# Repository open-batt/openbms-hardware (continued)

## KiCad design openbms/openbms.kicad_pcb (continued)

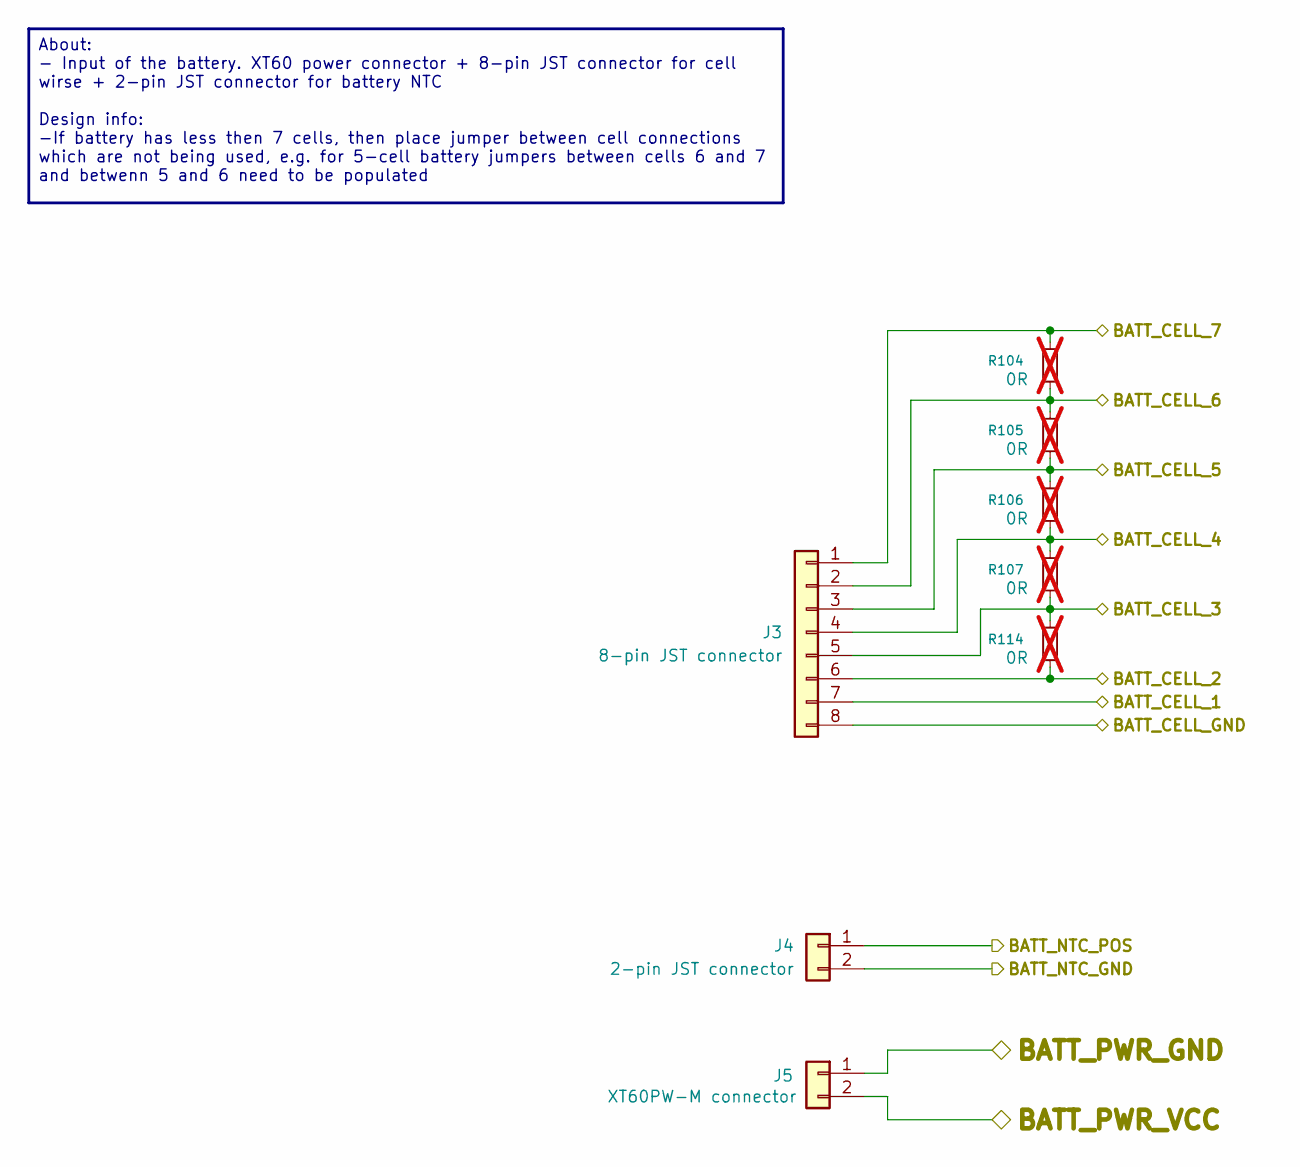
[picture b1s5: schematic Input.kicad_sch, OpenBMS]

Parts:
J3: 8-pin JST connector; JST_XH_S8B-XH-A_1x08_P2.50mm_Horizontal; Manufacturer_Part_Number S8B-XH-A
J4: 2-pin JST connector; JST_XH_S2B-XH-A_1x02_P2.50mm_Horizontal; Manufacturer_Part_Number S2B-XH-A
J5: XT60PW-M connector; AMASS_XT60PW-M_1x02_P7.20mm_Horizontal; Manufacturer_Part_Number XT60PW-M
R104, R105, R106, R107, R114: 0R; R_0402_1005Metric; Manufacturer_Part_Number CR0402AJ/-000GAS; not fitted

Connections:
+3V3: J4.1; also elsewhere on the board
/ADC/BATT_CS_POS: J5.1; also elsewhere on the board
/ADC/CELL_1: J3.7; also elsewhere on the board
/ADC/CELL_2: J3.6, R114.2; also elsewhere on the board
/ADC/CELL_3: J3.5, R107.2, R114.1; also elsewhere on the board
/ADC/CELL_4: J3.4, R106.2, R107.1; also elsewhere on the board
/ADC/CELL_5: J3.3, R105.2, R106.1; also elsewhere on the board
/ADC/CELL_6: J3.2, R104.2, R105.1; also elsewhere on the board
/ADC/CELL_7: J3.1, R104.1; also elsewhere on the board
/FETs/BATT_PWR_VCC: J5.2; also elsewhere on the board
/MCU/NTC: J4.2; also elsewhere on the board
GND_BATT_CELL: J3.8; also elsewhere on the board

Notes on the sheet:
About: - Input of the battery. XT60 power connector + 8-pin JST connector for cell wirse + 2-pin JST connector for battery NTC Design info: -If battery has less then 7 cells, then place jumper between cell connections which are not being used, e.g. for 5-cell battery jumpers between cells 6 and 7 a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

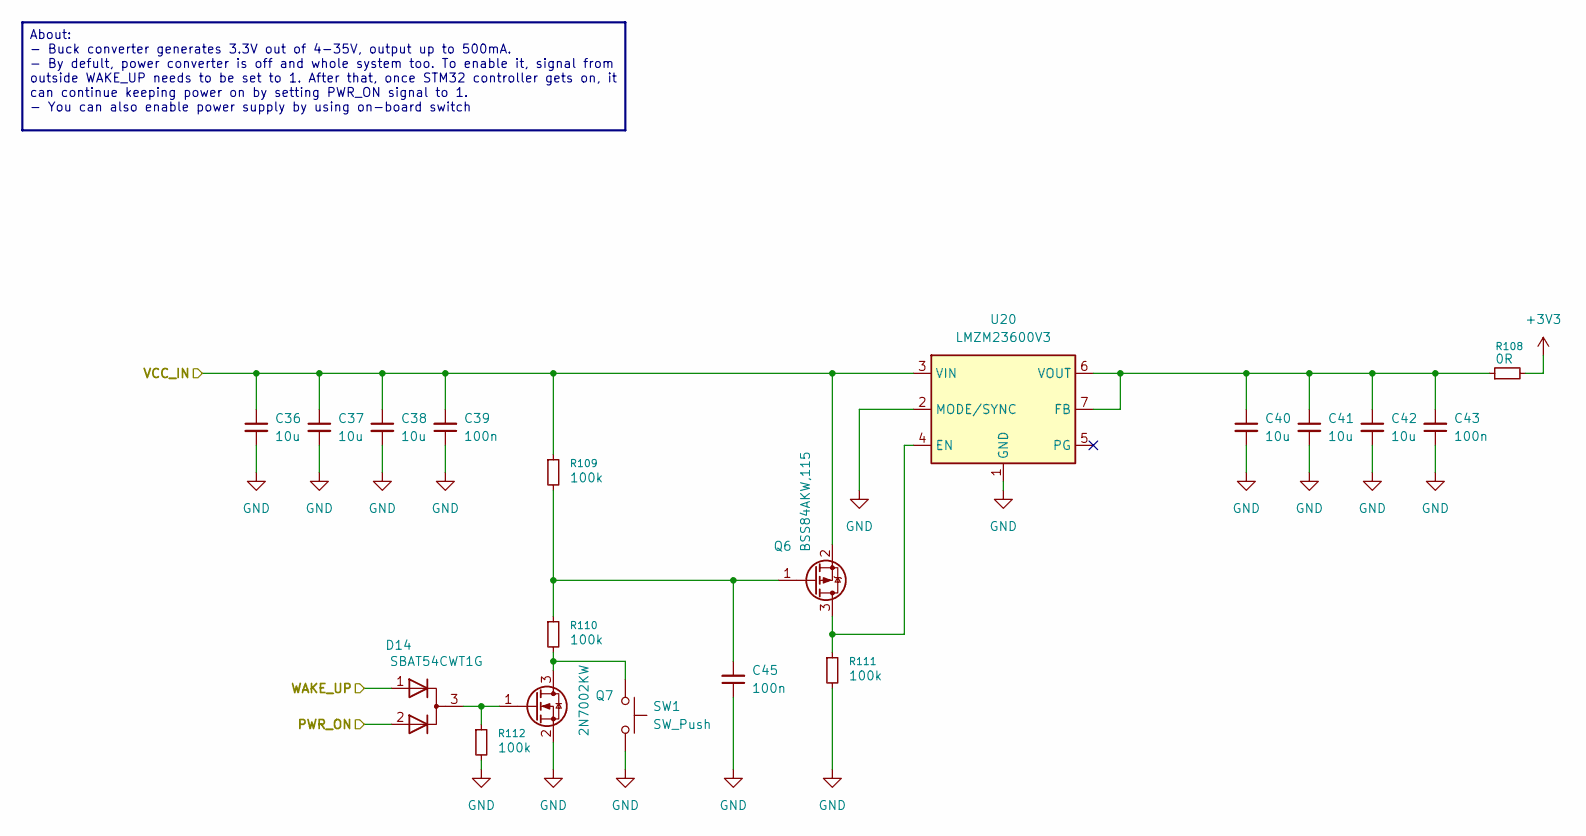
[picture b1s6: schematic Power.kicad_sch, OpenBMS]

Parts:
C36, C37, C38, C40, C41, C42: 10u; C_1206_3216Metric; Manufacturer_Part_Number CL31A106MBHNNNE
C39, C43, C45: 100n; C_0402_1005Metric; Manufacturer_Part_Number GRM155R71A104KA01D
D14: SBAT54CWT1G; SOT-323_SC-70; Manufacturer_Part_Number SBAT54CWT1G
Q6: BSS84AKW,115; SOT-323_SC-70; Manufacturer_Part_Number BSS84AKW,115
Q7: 2N7002KW; SOT-323_SC-70; Manufacturer_Part_Number 2N7002KW
R108: 0R; R_0402_1005Metric; Manufacturer_Part_Number CR0402AJ/-000GAS
R109, R110, R111, R112: 100k; R_0402_1005Metric; Manufacturer_Part_Number RC0402FR-07100KL
SW1: SW_Push; 435451019820; Manufacturer_Part_Number 435451019820
U20: LMZM23600V3; Texas_SIL0010A_MicroSiP-10-1EP_3.8x3mm_P0.6mm_EP0.7x2.9mm_T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; Manufacturer_Part_Number LMZM23600V3SILR

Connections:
+3V3: R108.2; also elsewhere on the board
/FETs/BATT_PWR_VCC_FUSED: C36.1, C37.1, C38.1, C39.2, Q6.2 (S), R109.1, U20.3 (VIN); also elsewhere on the board
/MCU/PWR_ON: D14.2 (A); also elsewhere on the board
/MCU/WAKE_UP: D14.1 (A); also elsewhere on the board
GND: C36.2, C37.2, C38.2, C39.1, C40.2, C41.2, C42.2, C43.1, C45.1, Q7.2 (S), R111.2, R112.2, SW1.2, U20.1 (GND), U20.2 (MODE/SYNC), U20.11 (GND); also elsewhere on the board
unnamed: D14.3 (K), Q7.1 (G), R112.1
unnamed: Q6.3 (D), R111.1, U20.4 (EN)
unnamed: C45.2, Q6.1 (G), R109.2, R110.1
unnamed: Q7.3 (D), R110.2, SW1.1
unnamed: C40.1, C41.1, C42.1, C43.2, R108.1, U20.6 (VOUT), U20.7 (FB)

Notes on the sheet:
About: - Buck converter generates 3.3V out of 4-35V, output up to 500mA. - By defult, power converter is off and whole system too. To enable it, signal from outside WAKE_UP needs to be set to 1. After that, once STM32 controller gets on, it can continue keeping power on by setting PWR_ON signal to 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

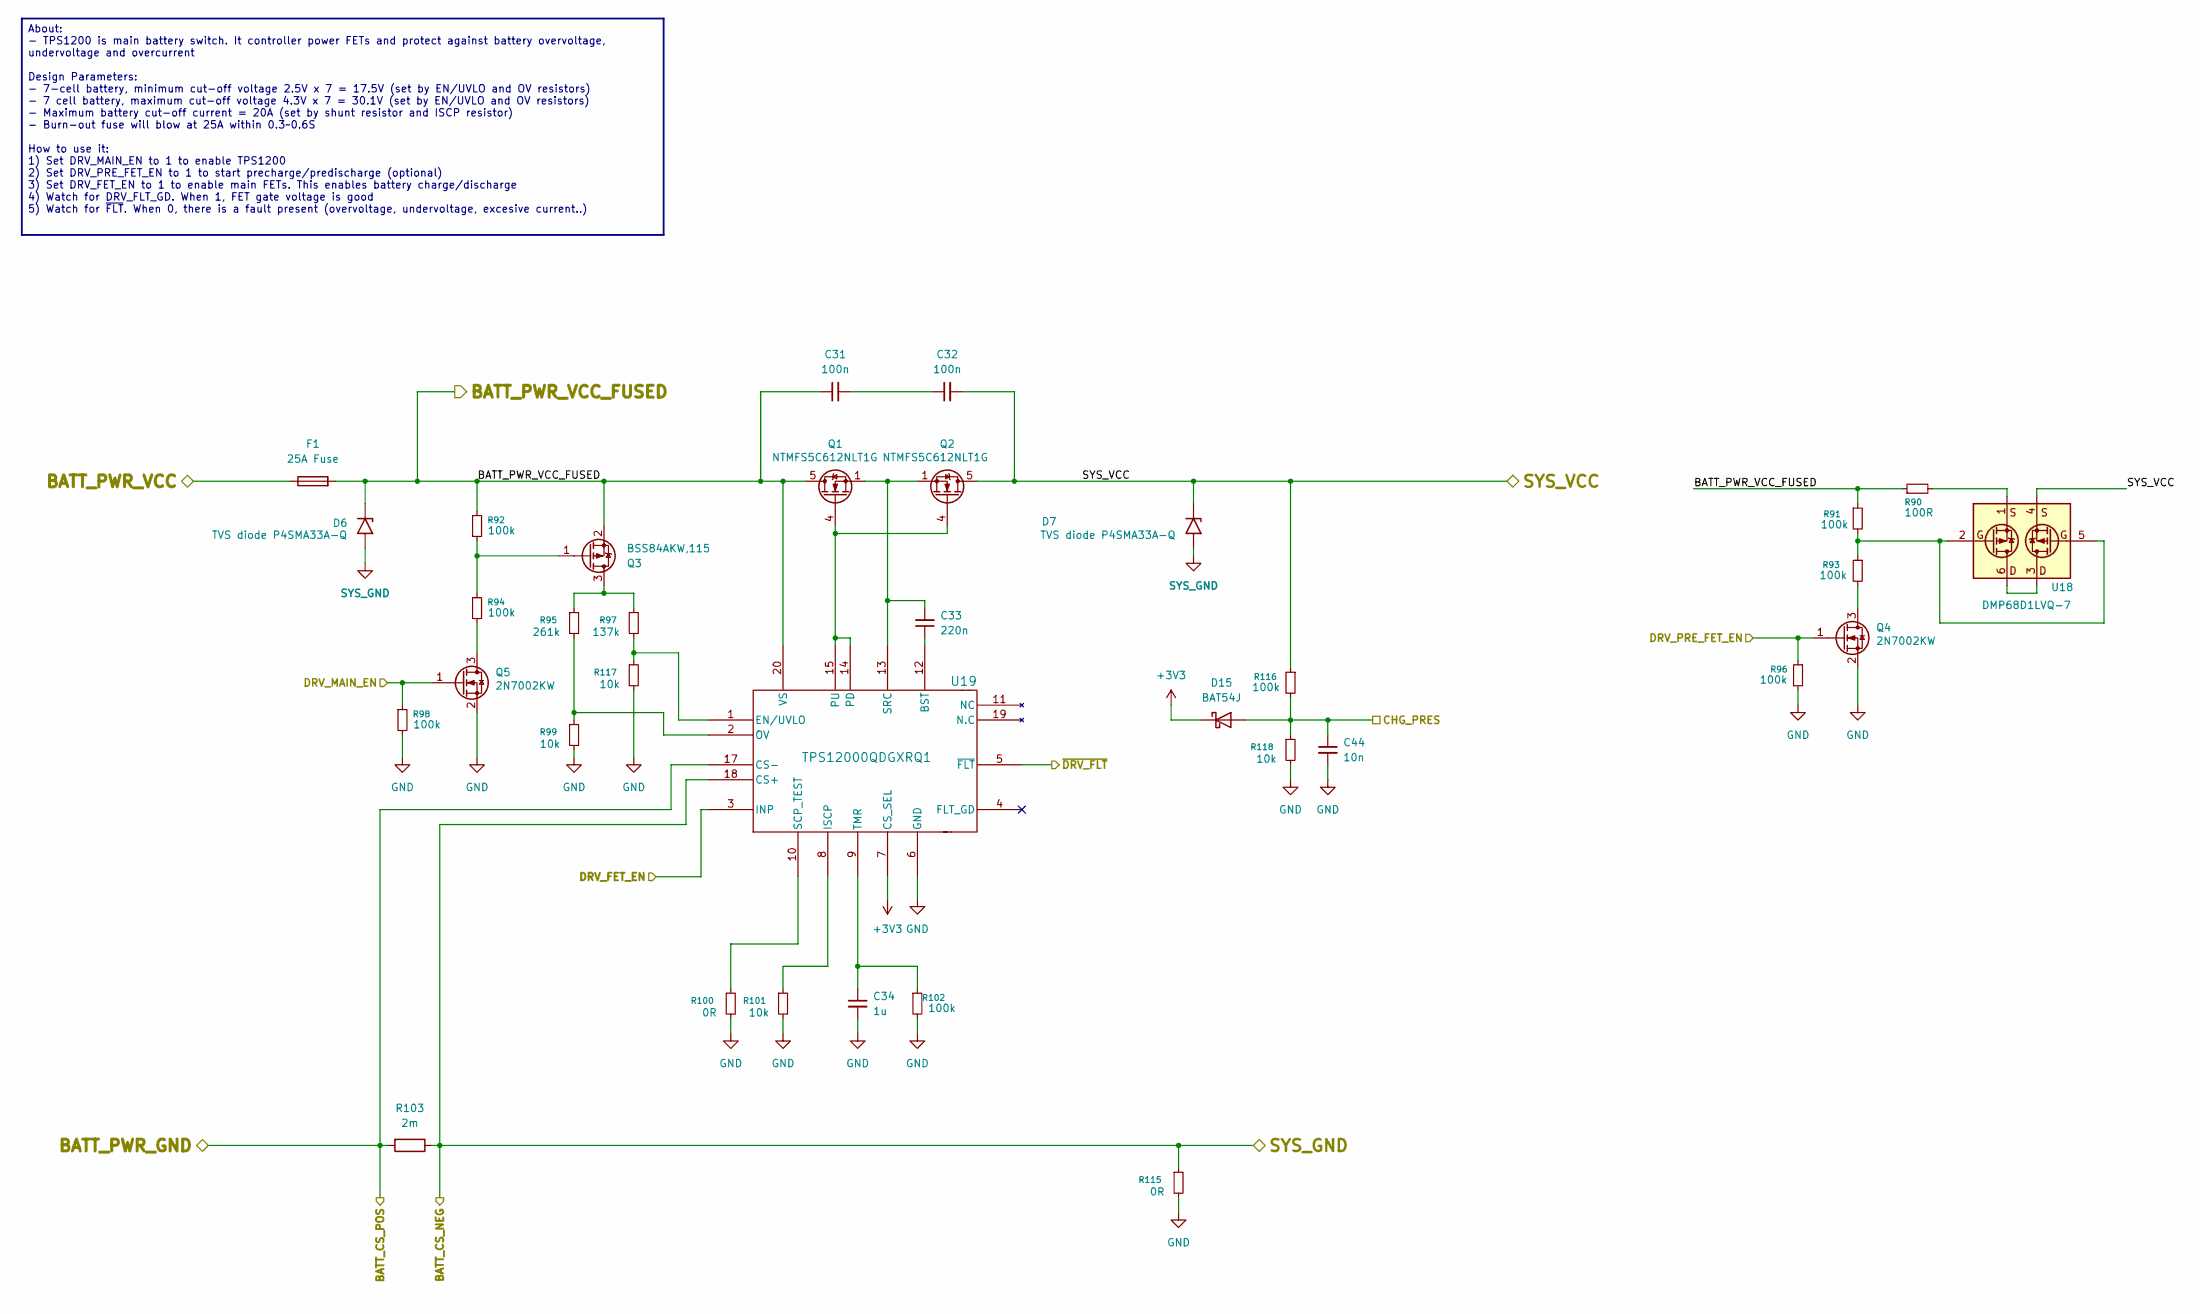
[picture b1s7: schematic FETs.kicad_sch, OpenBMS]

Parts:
C31, C32: 100n; C_0402_1005Metric; Manufacturer_Part_Number GRM155R71A104KA01D
C33: 220n; C_0603_1608Metric; Manufacturer_Part_Number CL10E224KA84PNC
C34: 1u; C_0402_1005Metric; Manufacturer_Part_Number C0402C105K8PACTU
C44: 10n; C_0402_1005Metric; Manufacturer_Part_Number C0402C103K5REC7411
D6, D7: TVS diode P4SMA33A-Q; D_SMA; Manufacturer_Part_Number P4SMA33A-Q
D15: BAT54J; D_SOD-323F
F1: 25A Fuse; Fuse_1206_3216Metric; Manufacturer_Part_Number SF-1206HV25M-2
Q1, Q2: NTMFS5C612NLT1G; ONSemi_SO-8FL_488AA; Manufacturer_Part_Number NTMFS5C612NLT1G
Q3: BSS84AKW,115; SOT-323_SC-70; Manufacturer_Part_Number BSS84AKW,115
Q4, Q5: 2N7002KW; SOT-323_SC-70; Manufacturer_Part_Number 2N7002KW
R90: 100R; R_2512_6332Metric; Manufacturer_Part_Number 3521100RFT
R91, R92, R93, R94, R96, R98, R102, R116: 100k; R_0402_1005Metric; Manufacturer_Part_Number RC0402FR-07100KL
R95: 261k; R_0402_1005Metric; Manufacturer_Part_Number RC0402FR-07261KL
R97: 137k; R_0402_1005Metric; Manufacturer_Part_Number RC0402FR-07137KL
R99, R101, R117, R118: 10k; R_0402_1005Metric; Manufacturer_Part_Number RMCF0402FT10K0
R100: 0R; R_0402_1005Metric; Manufacturer_Part_Number CR0402AJ/-000GAS
R103: 2m; 3920; Manufacturer_Part_Number SEWF3920D2L00P9
R115: 0R; R_0805_2012Metric; Manufacturer_Part_Number RMCF0805ZT0R00
U18: DMP68D1LVQ-7; SOTFL50P162X60-6N; Manufacturer_Part_Number DMP68D1LVQ-7; Mouser Part Number 621-DMP68D1LVQ-7
U19: TPS12000QDGXRQ1; VSSOP19_DGX_TEX; Manufacturer_Part_Number TPS12000QDGXRQ1

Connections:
+3V3: D15.1 (K), U19.7 (CS_SEL); also elsewhere on the board
/ADC/BATT_CS_POS: R103.2, U19.17 (CS-); also elsewhere on the board
/FETs/BATT_PWR_VCC: F1.1; also elsewhere on the board
/FETs/BATT_PWR_VCC_FUSED: C31.1, D6.1 (A1), F1.2, Q1.5 (D), Q3.2 (S), R90.1, R91.1, R92.1, U19.20 (VS); also elsewhere on the board
/FETs/CHG_PRES: C44.1, D15.2 (A), R116.2, R118.1; also elsewhere on the board
/FETs/DRV_FET_EN: U19.3 (INP); also elsewhere on the board
/FETs/DRV_MAIN_EN: Q5.1 (G), R98.1; also elsewhere on the board
/FETs/DRV_PRE_FET_EN: Q4.1 (G), R96.1; also elsewhere on the board
/FETs/SYS_VCC: C32.2, D7.1 (A1), Q2.5 (D), R116.1, U18.4; also elsewhere on the board
/FETs/~DRV_FLT: U19.5 (~FLT); also elsewhere on the board
GND: C34.2, C44.2, Q4.2 (S), Q5.2 (S), R96.2, R98.2, R99.2, R100.2, R101.2, R102.2, R115.2, R117.2, R118.2, U19.6 (GND); also elsewhere on the board
unnamed: C31.2, C32.1
unnamed: Q1.4 (G), Q2.4 (G), U19.14 (PD), U19.15 (PU)
unnamed: Q3.3 (D), R95.1, R97.1
unnamed: Q3.1 (G), R92.2, R94.1
unnamed: Q4.3 (D), R93.2
unnamed: Q5.3 (D), R94.2
unnamed: R90.2, U18.1
unnamed: R91.2, R93.1, U18.2, U18.5
unnamed: U18.3, U18.6
unnamed: C33.1, U19.12 (BST)
unnamed: R97.2, R117.1, U19.1 (EN/UVLO)
unnamed: R101.1, U19.8 (ISCP)
unnamed: R95.2, R99.1, U19.2 (OV)
unnamed: R100.1, U19.10 (SCP_TEST)
unnamed: C33.2, Q1.1 (S), Q1.2 (S), Q1.3 (S), Q2.1 (S), Q2.2 (S), Q2.3 (S), U19.13 (SRC)
unnamed: C34.1, R102.1, U19.9 (TMR)
SYS_GND: D6.2 (A2), D7.2 (A2), R103.1, R115.1, U19.18 (CS+); also elsewhere on the board

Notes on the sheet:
About: - TPS1200 is main battery switch. It controller power FETs and protect against battery overvoltage, undervoltage and overcurrent Design Parameters: - 7-cell battery, minimum cut-off voltage 2.5V x 7 = 17.5V (set by EN/UVLO and OV resistors) - 7 cell battery, maximum cut-off voltage 4.3V x 7 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

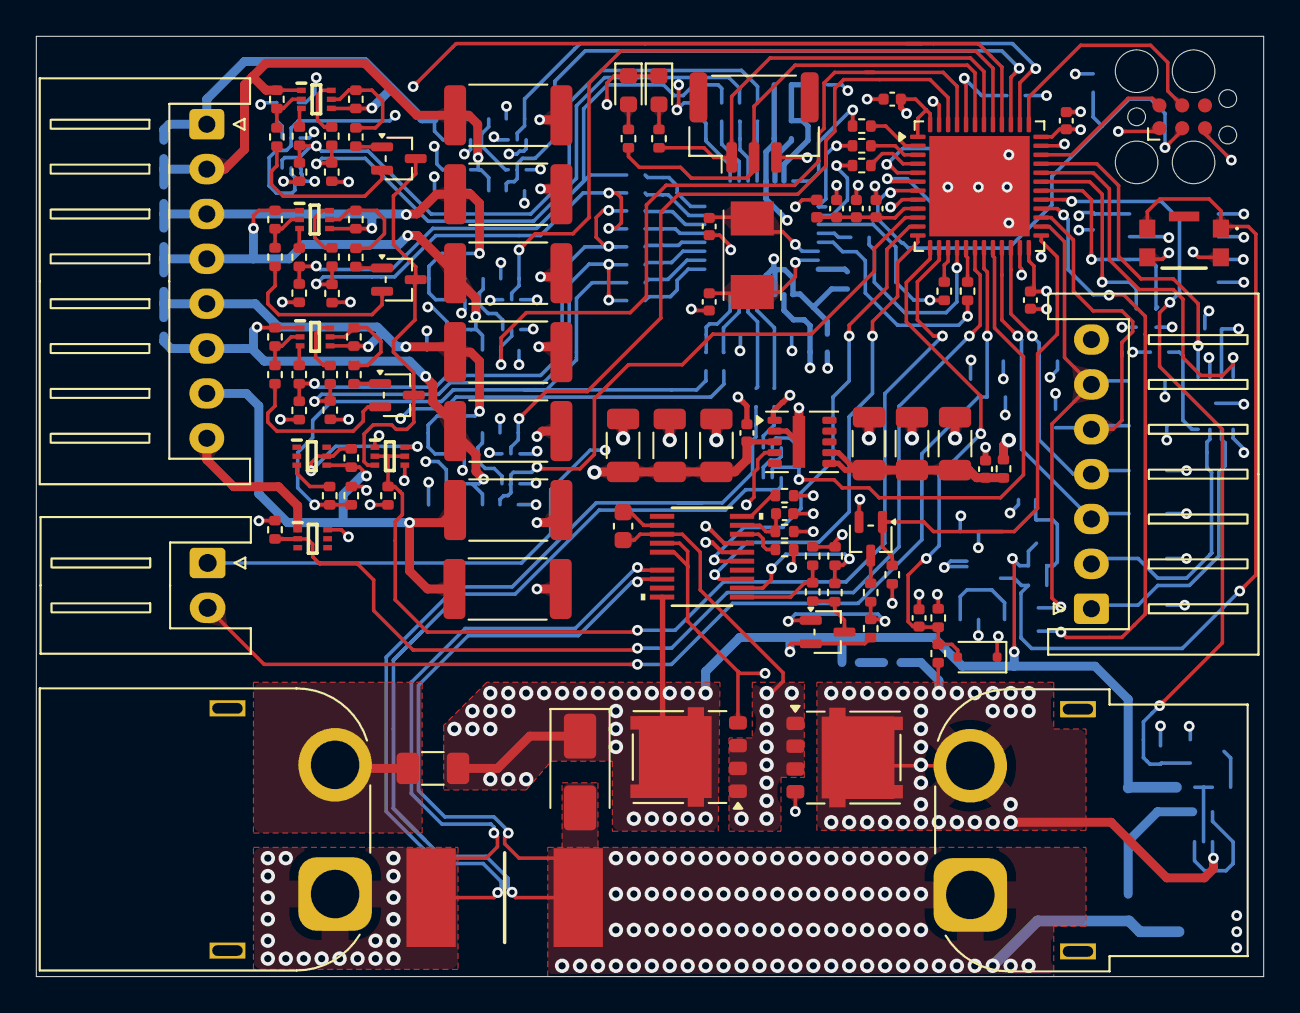
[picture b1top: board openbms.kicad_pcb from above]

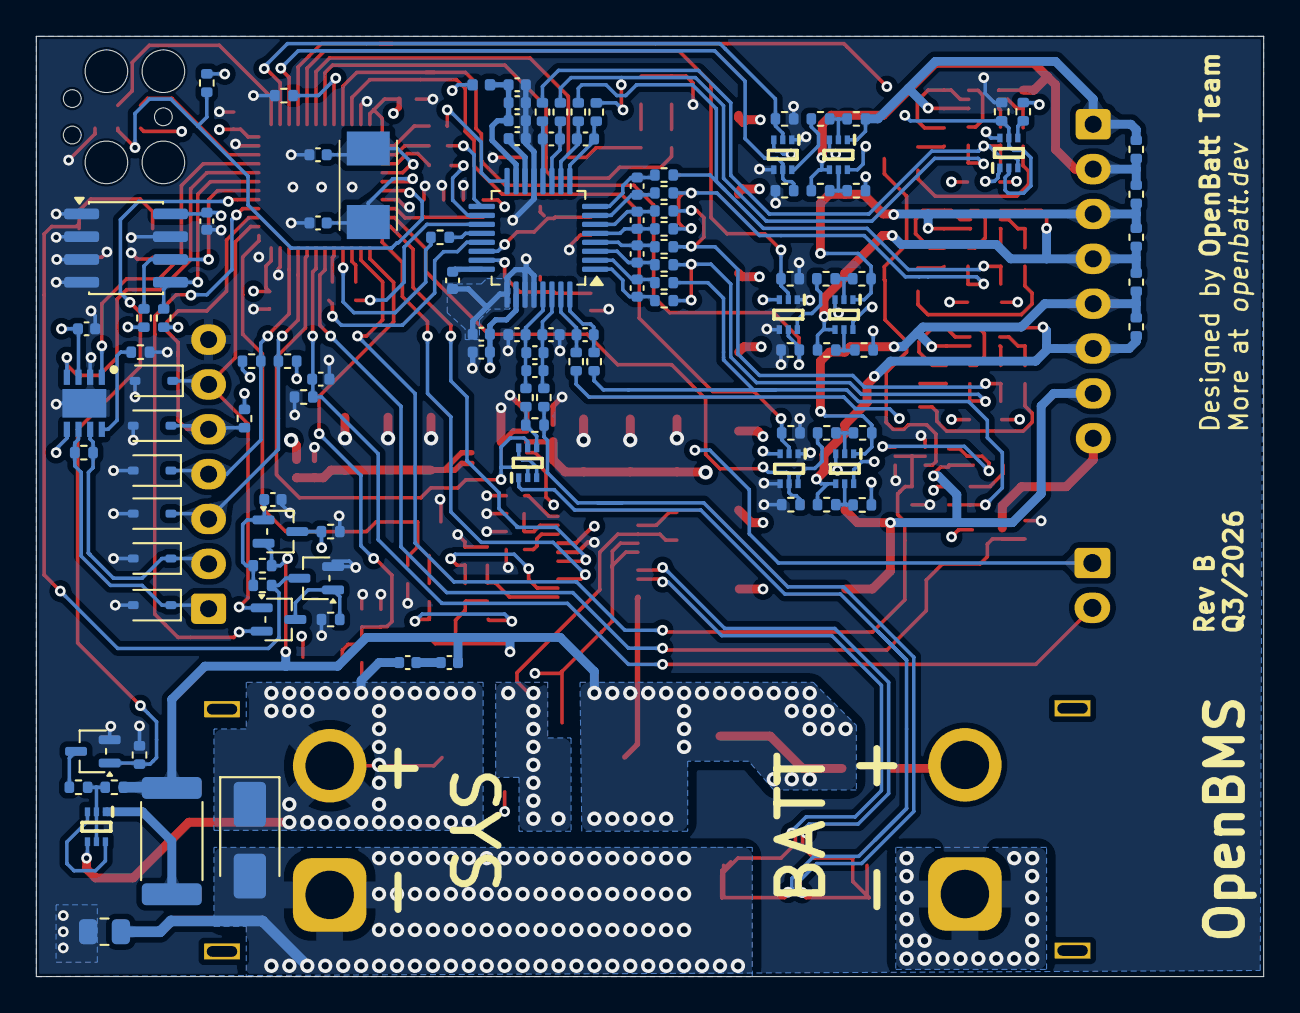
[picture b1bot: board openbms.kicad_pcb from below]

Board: 4 copper layers, 68.4 x 52.4 mm, 220 parts (113 on the bottom side), 158 nets.

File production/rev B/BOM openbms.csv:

Reference,Qty,Value,Manufacturer_Part_Number,Package
"C1,C2,C4,C6,C8,C10,C11,C12,C13,C15,C17,C18,C20,C21,C22,C23,C25,C29,C30,C31,C32,C39,C43,C45",24,100n,GRM155R71A104KA01D,0402
C3,1,100p,CL05C101JB5NNNC,0402
"C5,C9,C26,C34",4,1u,C0402C105K8PACTU,0402
"C7,C24,C35,C44",4,10n,C0402C103K5REC7411,0402
"C14,C16,C27,C28",4,18pF,GRM1555C1H180JA01D,0402
C19,1,220n,GRM155R71A224KE01J,0402
C33,1,220n,CL10E224KA84PNC,0603
"C36,C37,C38,C40,C41,C42",6,10u,CL31A106MBHNNNE,1206
"D1,D2,D3,D14",4,SBAT54CWT1G,SBAT54CWT1G,SOT-323
D4,1,Green LED,LTST-C190GKT,0603
D5,1,Red LED,LTST-C190KRKT,0603
"D6,D7",2,TVS diode P4SMA33A-Q,P4SMA33A-Q,DO-214AC
"D8,D9,D10,D11,D12,D13",6,TVS diode DBLC03CIQ-7,DBLC03CIQ-7,SOD-323
D15,1,BAT54J,BAT54J,SOD-323
F1,1,25A Fuse,SF-1206HV25M-2,1206
J1,1,3-pin JST connector,BM03B-GHS-TBT,3-pin JST connector
J3,1,8-pin JST connector,S8B-XH-A,8-pin JST connector
J4,1,2-pin JST connector,S2B-XH-A,2-pin JST connector
J5,1,XT60PW-M connector,XT60PW-M,XT60PW-M connector
J6,1,XT60PW-F connector,XT60PW-F,XT60PW-F connector
J7,1,7-pin JST connector,S7B-XH-A,7-pin JST connector
"L1,L2",2,600R @ 100MHz,BLM15PX601SN1D,0402
"Q1,Q2",2,NTMFS5C612NLT1G,NTMFS5C612NLT1G,5-DFN (5x6) (8-SOFL)
"Q3,Q6",2,"BSS84AKW,115","BSS84AKW,115",SOT-323
"Q4,Q5,Q7",3,2N7002KW,2N7002KW,SOT-323
"R1,R2,R3,R4,R6,R7,R9,R14,R21,R22,R25,R29,R30,R31,R34,R35,R49,R50,R54,R58,R62,R63,R64,R65,R66,R91,R92,R93,R94,R96,R98,R102,R109,R110,R111,R112,R116,R119",38,100k,RC0402FR-07100KL,0402
"R5,R8",2,100R,RMCF0402FT100R,0402
"R10,R11,R41,R42,R67,R68,R74",7,50R,RNCL2512FT50R0,2512
"R12,R13,R27,R28,R56,R57,R69",7,"68k,0.1%",RT0402BRD0768KL,0402
"R15,R16,R36,R37,R60,R61,R73",7,"2k,0.1%",RT0402BRD072KL,0402
"R17,R20,R23,R24,R26,R32,R33,R43,R45,R48,R51,R55,R59",13,"1k,0.1%",RT0402BRD071KL,0402
"R18,R19,R52,R53,R70,R71,R72,R75,R76,R78,R86,R99,R101,R117,R118",15,10k,RMCF0402FT10K0,0402
"R38,R39,R40,R44",4,33R,RC0402FR-0733RL,0402
"R46,R47",2,100R,RC0402FR-07100RL,0402
R77,1,"330R,0.1%",RT0402BRD07330RL,0402
"R79,R80",2,470R,RC0402FR-07470RL,0402
"R81,R87,R100,R108,R113",5,0R,CR0402AJ/-000GAS,0402
"R82,R83,R84,R88,R89",5,4.7k,RC0402JR-074K7L,0402
R85,1,120R,CRCW0402120RFKEDC,0402
R90,1,100R,3521100RFT,2512
R95,1,261k,RC0402FR-07261KL,0402
R97,1,137k,RC0402FR-07137KL,0402
R103,1,2m,SEWF3920D2L00P9,3920
R115,1,0R,RMCF0805ZT0R00,0805
SW1,1,SW_Push,435451019820,4.60mm x 2.80mm
"U1,U2,U4,U6,U8,U9,U10,U18",8,DMP68D1LVQ-7,DMP68D1LVQ-7,SOT-563
"U3,U7,U11,U12,U13,U14,U22",7,DMN601VK-7,DMN601VK-7,SOT-563
U5,1,ADS131M08xPBS,ADS131M08IPBS,32-TQFP
U15,1,STM32L431CCUx,STM32L431CCU6TR,48-UFQFPN
U16,1,TCAN3413DRBR,TCAN3413DRBR,8-VDFN
U17,1,32kbit EEPROM memory,M24256-DRMN8TP/K,8-SOIC
U19,1,TPS12000QDGXRQ1,TPS12000QDGXRQ1,19-VSSOP
U20,1,LMZM23600V3,LMZM23600V3SILR,3.8 x 3
Y1,1,8.192MHz,ECS-81.92-12-30Q-EN-TR,5.0 x 3.2
Y2,1,8MHz,ECS-80-12-30Q-DS-TR,5.0 x 3.2

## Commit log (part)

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2026-04-16 Initial release, schematic and PCB Layout for Rev A release
2026-04-16 Image added
2026-04-16 Images added
2026-04-16 Images resized
2026-04-21 Capacitor values in ADC increased from 10n to 100n, production files released
2026-04-28 Update README.md
    Readme updates
2026-06-05 Readme file updated, images and videos updated, links fixed
2026-06-05 Readme file updated
